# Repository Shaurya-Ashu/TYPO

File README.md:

# TYPO
It is a 80% keyboard containing 79 keys 1 rotary encoder and a custom touchpad button all together is powered by a raspberry pi pico .

# Schematics 
In KiCad 

# PCB 
It's a 2 layer simple pcb designed in KiCad .

it has a one pice silkscreen on the back 

# Case
It's a very simple case designed in fusion 360 .
It is designed around integrated plate mount with bottom plate .

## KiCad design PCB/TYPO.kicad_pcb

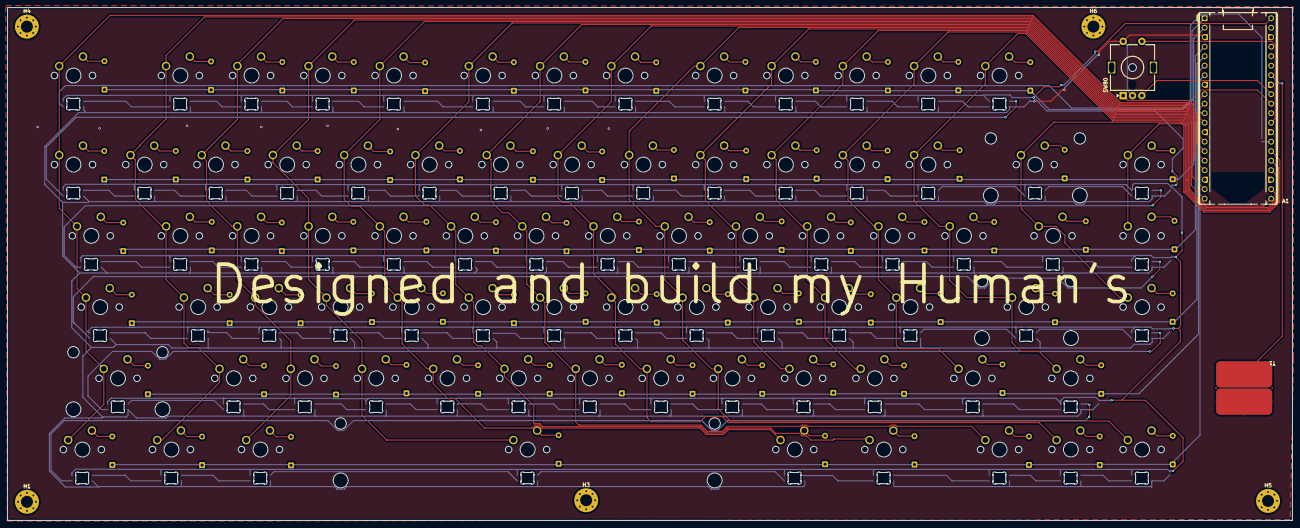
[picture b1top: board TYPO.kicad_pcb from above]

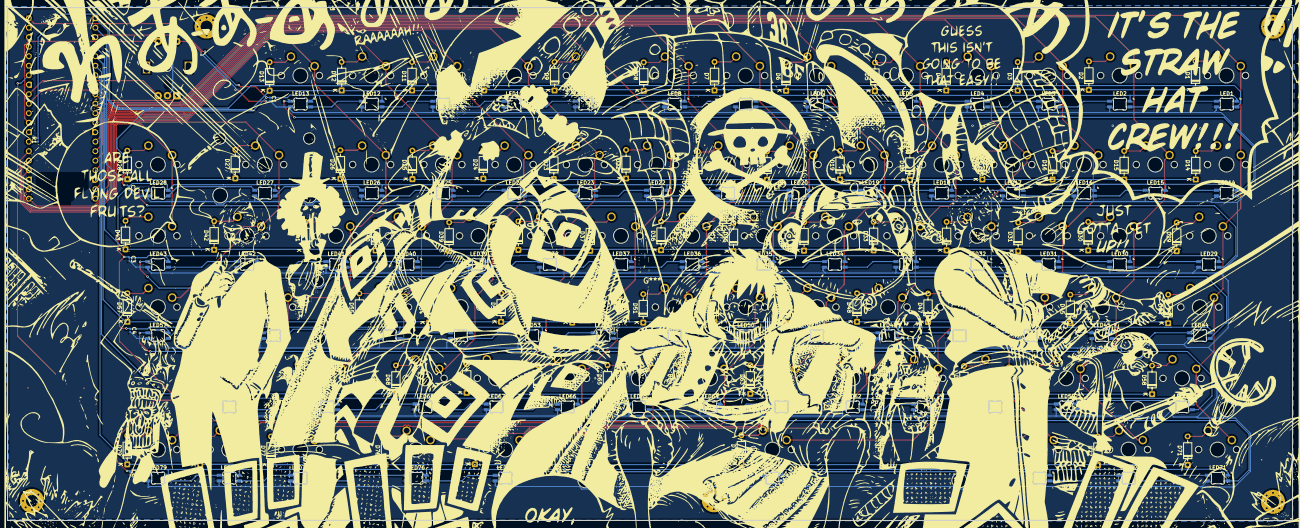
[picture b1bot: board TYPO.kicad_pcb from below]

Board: 2 copper layers, 343.6 x 137.1 mm, 256 parts (165 on the bottom side), 186 nets.

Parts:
A1: RaspberryPi_Pico; RaspberryPi_Pico_Common_THT
C1, C2, C3, C4, C5, C6: C; C_0201_0603Metric_Pad0.64x0.40mm_HandSolder
D1, D2, D3, D4, D5, D6, D7, D8, D9, D10, D11, D12, D13, D14, D15, D16, D17, D18, D19, D20, D21, D22, D23, D24, D25, D26, D27, D28, D29, D30, D31, D32, D33, D34, D35, D36, D37, D38, D39, D40, D41, D42, D43, D44, D45, D46, D47, D48, D49, D50, D51, D52, D53, D54, D55, D56, D57, D58, D59, D60, D61, D62, D63, D64, D65, D66, D67, D68, D69, D70, D71, D72, D73, D74, D75, D76, D77, D78, D79: 1N4148; D_DO-35_SOD27_P7.62mm_Horizontal
H1, H3, H4, H5, H6: MountingHole; MountingHole_3.2mm_M3_Pad_Via
LED1, LED2, LED3, LED4, LED5, LED6, LED7, LED8, LED9, LED10, LED11, LED12, LED13, LED14, LED15, LED16, LED17, LED18, LED19, LED20, LED21, LED22, LED23, LED24, LED25, LED26, LED27, LED28, LED29, LED30, LED31, LED32, LED33, LED34, LED35, LED36, LED37, LED38, LED39, LED40, LED41, LED42, LED43, LED44, LED45, LED46, LED47, LED48, LED49, LED50, LED51, LED52, LED53, LED54, LED55, LED56, LED57, LED58, LED59, LED60, LED61, LED62, LED63, LED64, LED65, LED66, LED67, LED68, LED69, LED70, LED71, LED72, LED73, LED74, LED75, LED76, LED77, LED78, LED79: SK6812MINI-E; LED_6028R
R1: R; R_0201_0603Metric_Pad0.64x0.40mm_HandSolder
S1: MX_stab; STAB_MX_6.25u
S2, S3: MX_stab; STAB_MX_2.25u
S4: MX_stab; STAB_MX_2u
SW1, SW2, SW3, SW4, SW5, SW6, SW7, SW8, SW9, SW10, SW11, SW12, SW13, SW14, SW15, SW16, SW17, SW18, SW19, SW20, SW21, SW22, SW23, SW24, SW25, SW26, SW27, SW28, SW29, SW30, SW31, SW32, SW33, SW34, SW35, SW36, SW37, SW38, SW39, SW40, SW41, SW42, SW43, SW44, SW45, SW46, SW47, SW48, SW49, SW50, SW51, SW52, SW53, SW54, SW55, SW56, SW57, SW58, SW59, SW60, SW61, SW62, SW63, SW64, SW65, SW66, SW67, SW68, SW69, SW70, SW71, SW72, SW73, SW74, SW75, SW76, SW77, SW78, SW79: SW_Push; SW_MX_1u
SW80: RotaryEncoder_Switch_MP; RotaryEncoder_Alps_EC11E-Switch_Vertical_H20mm_MountingHoles
T1: touch

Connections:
/A: A1.31 (GPIO26_ADC0), SW80.A
/B: A1.32 (GPIO27_ADC1), SW80.B
/C1: A1.9 (GPIO6), SW1.1, SW14.1, SW29.1, SW44.1, SW58.1, SW71.1
/C2: A1.10 (GPIO7), SW2.1, SW15.1, SW30.1, SW45.1, SW59.1, SW72.1
/C3: A1.11 (GPIO8), SW3.1, SW16.1, SW31.1, SW46.1, SW60.1, SW73.1
/C4: A1.12 (GPIO9), SW4.1, SW17.1, SW32.1, SW47.1, SW61.1, SW74.1
/C5: A1.14 (GPIO10), SW5.1, SW18.1, SW33.1, SW48.1, SW62.1, SW75.1
/C6: A1.15 (GPIO11), SW6.1, SW19.1, SW34.1, SW49.1, SW63.1, SW76.1
/C7: A1.16 (GPIO12), SW7.1, SW20.1, SW35.1, SW50.1, SW64.1, SW77.1
/C8: A1.17 (GPIO13), SW8.1, SW21.1, SW36.1, SW51.1, SW65.1, SW78.1
/C9: A1.19 (GPIO14), SW9.1, SW22.1, SW37.1, SW52.1, SW66.1, SW79.1
/C10: A1.20 (GPIO15), SW10.1, SW23.1, SW38.1, SW53.1, SW67.1
/C11: A1.21 (GPIO16), SW11.1, SW24.1, SW39.1, SW54.1, SW68.1
/C12: A1.22 (GPIO17), SW12.1, SW25.1, SW40.1, SW55.1, SW69.1
/C13: A1.24 (GPIO18), SW13.1, SW26.1, SW41.1, SW56.1, SW70.1
/C14: A1.25 (GPIO19), SW27.1, SW42.1, SW57.1
/C15: A1.26 (GPIO20), SW28.1, SW43.1
/R1: A1.1 (GPIO0), D1.1 (K), D2.1 (K), D3.1 (K), D4.1 (K), D5.1 (K), D6.1 (K), D7.1 (K), D8.1 (K), D9.1 (K), D10.1 (K), D11.1 (K), D12.1 (K), D13.1 (K)
/R2: A1.2 (GPIO1), D14.1 (K), D15.1 (K), D16.1 (K), D17.1 (K), D18.1 (K), D19.1 (K), D20.1 (K), D21.1 (K), D22.1 (K), D23.1 (K), D24.1 (K), D25.1 (K), D26.1 (K), D27.1 (K), D28.1 (K)
/R3: A1.4 (GPIO2), D29.1 (K), D30.1 (K), D31.1 (K), D32.1 (K), D33.1 (K), D34.1 (K), D35.1 (K), D36.1 (K), D37.1 (K), D38.1 (K), D39.1 (K), D40.1 (K), D41.1 (K), D42.1 (K), D43.1 (K)
/R4: A1.5 (GPIO3), D44.1 (K), D45.1 (K), D46.1 (K), D47.1 (K), D48.1 (K), D49.1 (K), D50.1 (K), D51.1 (K), D52.1 (K), D53.1 (K), D54.1 (K), D55.1 (K), D56.1 (K), D57.1 (K)
/R5: A1.6 (GPIO4), D58.1 (K), D59.1 (K), D60.1 (K), D61.1 (K), D62.1 (K), D63.1 (K), D64.1 (K), D65.1 (K), D66.1 (K), D67.1 (K), D68.1 (K), D69.1 (K), D70.1 (K)
/R6: A1.7 (GPIO5), D71.1 (K), D72.1 (K), D73.1 (K), D74.1 (K), D75.1 (K), D76.1 (K), D77.1 (K), D78.1 (K), D79.1 (K)
/SW1: A1.29 (GPIO22), SW80.S1
/touch: A1.34 (GPIO28_ADC2), T1.1 (out)
GND: A1.3 (GND), A1.8 (GND), A1.13 (GND), A1.18 (GND), A1.23 (GND), A1.28 (GND), A1.38 (GND), C1.2, C2.2, C3.2, C4.2, C5.2, C6.2, LED1.1 (VDD), LED2.1 (VDD), LED3.1 (VDD), LED4.1 (VDD), LED5.1 (VDD), LED6.1 (VDD), LED7.1 (VDD), LED8.1 (VDD), LED9.1 (VDD), LED10.1 (VDD), LED11.1 (VDD), LED12.1 (VDD), LED13.1 (VDD), LED14.1 (VDD), LED15.1 (VDD), LED16.1 (VDD), LED17.1 (VDD), LED18.1 (VDD), LED19.1 (VDD), LED20.1 (VDD), LED21.1 (VDD), LED22.1 (VDD), LED23.1 (VDD), LED24.1 (VDD), LED25.1 (VDD), LED26.1 (VDD), LED27.1 (VDD), LED28.1 (VDD), LED29.1 (VDD), LED30.1 (VDD), LED31.1 (VDD), LED32.1 (VDD), LED33.1 (VDD), LED34.1 (VDD), LED35.1 (VDD), LED36.1 (VDD), LED37.1 (VDD), LED38.1 (VDD), LED39.1 (VDD), LED40.1 (VDD), LED41.1 (VDD), LED42.1 (VDD), LED43.1 (VDD), LED44.1 (VDD), LED45.1 (VDD), LED46.1 (VDD), LED47.1 (VDD), LED48.1 (VDD), LED49.1 (VDD), LED50.1 (VDD), LED51.1 (VDD), LED52.1 (VDD), LED53.1 (VDD), LED54.1 (VDD), LED55.1 (VDD), LED56.1 (VDD), LED57.1 (VDD), LED58.1 (VDD), LED59.1 (VDD), LED60.1 (VDD), LED61.1 (VDD), LED62.1 (VDD), LED63.1 (VDD), LED64.1 (VDD), LED65.1 (VDD), LED66.1 (VDD), LED67.1 (VDD), LED68.1 (VDD), LED69.1 (VDD), LED70.1 (VDD), LED71.1 (VDD), LED72.1 (VDD), LED73.1 (VDD), LED74.1 (VDD), LED75.1 (VDD), LED76.1 (VDD), LED77.1 (VDD), LED78.1 (VDD), LED79.1 (VDD), SW80.C, SW80.S2, T1.2 (gnd)
unnamed: A1.27 (GPIO21), R1.1
unnamed: D1.2 (A), SW1.2
unnamed: D2.2 (A), SW2.2
unnamed: D3.2 (A), SW3.2
unnamed: D4.2 (A), SW4.2
unnamed: D5.2 (A), SW5.2
unnamed: D6.2 (A), SW6.2
unnamed: D7.2 (A), SW7.2
unnamed: D8.2 (A), SW8.2
unnamed: D9.2 (A), SW9.2
unnamed: D10.2 (A), SW10.2
unnamed: D11.2 (A), SW11.2
unnamed: D12.2 (A), SW12.2
unnamed: D13.2 (A), SW13.2
unnamed: D14.2 (A), SW14.2
unnamed: D15.2 (A), SW15.2
unnamed: D16.2 (A), SW16.2
unnamed: D17.2 (A), SW17.2
unnamed: D18.2 (A), SW18.2
unnamed: D19.2 (A), SW19.2
unnamed: D20.2 (A), SW20.2
unnamed: D21.2 (A), SW21.2
unnamed: D22.2 (A), SW22.2
unnamed: D23.2 (A), SW23.2
unnamed: D24.2 (A), SW24.2
unnamed: D25.2 (A), SW25.2
unnamed: D26.2 (A), SW26.2
unnamed: D27.2 (A), SW27.2
unnamed: D28.2 (A), SW28.2
unnamed: D29.2 (A), SW29.2
unnamed: D30.2 (A), SW30.2
unnamed: D31.2 (A), SW31.2
unnamed: D32.2 (A), SW32.2
unnamed: D33.2 (A), SW33.2
unnamed: D34.2 (A), SW34.2
unnamed: D35.2 (A), SW35.2
unnamed: D36.2 (A), SW36.2
unnamed: D37.2 (A), SW37.2
unnamed: D38.2 (A), SW38.2
unnamed: D39.2 (A), SW39.2
unnamed: D40.2 (A), SW40.2
unnamed: D41.2 (A), SW41.2
unnamed: D42.2 (A), SW42.2
unnamed: D43.2 (A), SW43.2
unnamed: D44.2 (A), SW44.2
unnamed: D45.2 (A), SW45.2
unnamed: D46.2 (A), SW46.2
unnamed: D47.2 (A), SW47.2
unnamed: D48.2 (A), SW48.2
unnamed: D49.2 (A), SW49.2
unnamed: D50.2 (A), SW50.2
unnamed: D51.2 (A), SW51.2
unnamed: D52.2 (A), SW52.2
unnamed: D53.2 (A), SW53.2
unnamed: D54.2 (A), SW54.2
unnamed: D55.2 (A), SW55.2
unnamed: D56.2 (A), SW56.2
unnamed: D57.2 (A), SW57.2
unnamed: D58.2 (A), SW58.2
unnamed: D59.2 (A), SW59.2
unnamed: D60.2 (A), SW60.2
unnamed: D61.2 (A), SW61.2
unnamed: D62.2 (A), SW62.2
unnamed: D63.2 (A), SW63.2
unnamed: D64.2 (A), SW64.2
unnamed: D65.2 (A), SW65.2
unnamed: D66.2 (A), SW66.2
unnamed: D67.2 (A), SW67.2
unnamed: D68.2 (A), SW68.2
unnamed: D69.2 (A), SW69.2
unnamed: D70.2 (A), SW70.2
unnamed: D71.2 (A), SW71.2
unnamed: D72.2 (A), SW72.2
unnamed: D73.2 (A), SW73.2
unnamed: D74.2 (A), SW74.2
unnamed: D75.2 (A), SW75.2
unnamed: D76.2 (A), SW76.2
unnamed: D77.2 (A), SW77.2
unnamed: D78.2 (A), SW78.2
unnamed: D79.2 (A), SW79.2
unnamed: LED1.2 (DOUT), LED2.3 (DIN)
unnamed: LED2.2 (DOUT), LED3.3 (DIN)
unnamed: LED3.2 (DOUT), LED4.3 (DIN)
unnamed: LED4.2 (DOUT), LED5.3 (DIN)
unnamed: LED5.2 (DOUT), LED6.3 (DIN)
unnamed: LED6.2 (DOUT), LED7.3 (DIN)
unnamed: LED7.2 (DOUT), LED8.3 (DIN)
unnamed: LED8.2 (DOUT), LED9.3 (DIN)
unnamed: LED9.2 (DOUT), LED10.3 (DIN)
unnamed: LED10.2 (DOUT), LED11.3 (DIN)
unnamed: LED11.2 (DOUT), LED12.3 (DIN)
unnamed: LED12.2 (DOUT), LED13.3 (DIN)
unnamed: LED13.2 (DOUT), LED14.3 (DIN)
unnamed: LED14.2 (DOUT), LED15.3 (DIN)
unnamed: LED15.2 (DOUT), LED16.3 (DIN)
unnamed: LED16.2 (DOUT), LED17.3 (DIN)
unnamed: LED17.2 (DOUT), LED18.3 (DIN)
unnamed: LED18.2 (DOUT), LED19.3 (DIN)
unnamed: LED19.2 (DOUT), LED20.3 (DIN)
unnamed: LED20.2 (DOUT), LED21.3 (DIN)
unnamed: LED21.2 (DOUT), LED22.3 (DIN)
unnamed: LED22.2 (DOUT), LED23.3 (DIN)
unnamed: LED23.2 (DOUT), LED24.3 (DIN)
unnamed: LED24.2 (DOUT), LED25.3 (DIN)
unnamed: LED25.2 (DOUT), LED26.3 (DIN)
unnamed: LED26.2 (DOUT), LED27.3 (DIN)
unnamed: LED27.2 (DOUT), LED28.3 (DIN)
unnamed: LED28.2 (DOUT), LED29.3 (DIN)
unnamed: LED29.2 (DOUT), LED30.3 (DIN)
unnamed: LED30.2 (DOUT), LED31.3 (DIN)
unnamed: LED31.2 (DOUT), LED32.3 (DIN)
unnamed: LED32.2 (DOUT), LED33.3 (DIN)
unnamed: LED33.2 (DOUT), LED34.3 (DIN)
unnamed: LED34.2 (DOUT), LED35.3 (DIN)
unnamed: LED35.2 (DOUT), LED36.3 (DIN)
unnamed: LED36.2 (DOUT), LED37.3 (DIN)
unnamed: LED37.2 (DOUT), LED38.3 (DIN)
unnamed: LED38.2 (DOUT), LED39.3 (DIN)
unnamed: LED39.2 (DOUT), LED40.3 (DIN)
unnamed: LED40.2 (DOUT), LED41.3 (DIN)
unnamed: LED41.2 (DOUT), LED42.3 (DIN)
unnamed: LED42.2 (DOUT), LED43.3 (DIN)
unnamed: LED43.2 (DOUT), LED44.3 (DIN)
unnamed: LED44.2 (DOUT), LED45.3 (DIN)
unnamed: LED45.2 (DOUT), LED46.3 (DIN)
unnamed: LED46.2 (DOUT), LED47.3 (DIN)
unnamed: LED47.2 (DOUT), LED48.3 (DIN)
unnamed: LED48.2 (DOUT), LED49.3 (DIN)
unnamed: LED49.2 (DOUT), LED50.3 (DIN)
unnamed: LED50.2 (DOUT), LED51.3 (DIN)
unnamed: LED51.2 (DOUT), LED52.3 (DIN)
unnamed: LED52.2 (DOUT), LED53.3 (DIN)
unnamed: LED53.2 (DOUT), LED54.3 (DIN)
unnamed: LED54.2 (DOUT), LED55.3 (DIN)
unnamed: LED55.2 (DOUT), LED56.3 (DIN)
unnamed: LED56.2 (DOUT), LED57.3 (DIN)
unnamed: LED57.2 (DOUT), LED58.3 (DIN)
unnamed: LED58.2 (DOUT), LED59.3 (DIN)
unnamed: LED59.2 (DOUT), LED60.3 (DIN)
unnamed: LED60.2 (DOUT), LED61.3 (DIN)
unnamed: LED61.2 (DOUT), LED62.3 (DIN)
unnamed: LED62.2 (DOUT), LED63.3 (DIN)
unnamed: LED63.2 (DOUT), LED64.3 (DIN)
unnamed: LED64.2 (DOUT), LED65.3 (DIN)
unnamed: LED65.2 (DOUT), LED66.3 (DIN)
unnamed: LED66.2 (DOUT), LED67.3 (DIN)
unnamed: LED67.2 (DOUT), LED68.3 (DIN)
unnamed: LED68.2 (DOUT), LED69.3 (DIN)
unnamed: LED69.2 (DOUT), LED70.3 (DIN)
unnamed: LED70.2 (DOUT), LED71.3 (DIN)
unnamed: LED71.2 (DOUT), LED72.3 (DIN)
unnamed: LED72.2 (DOUT), LED73.3 (DIN)
unnamed: LED73.2 (DOUT), LED74.3 (DIN)
unnamed: LED74.2 (DOUT), LED75.3 (DIN)
unnamed: LED75.2 (DOUT), LED76.3 (DIN)
unnamed: LED76.2 (DOUT), LED77.3 (DIN)
unnamed: LED77.2 (DOUT), LED78.3 (DIN)
unnamed: LED78.2 (DOUT), LED79.3 (DIN)
RGB: LED1.3 (DIN), R1.2
VCC: A1.40 (VBUS), C1.1, C2.1, C3.1, C4.1, C5.1, C6.1, LED1.4 (VSS), LED2.4 (VSS), LED3.4 (VSS), LED4.4 (VSS), LED5.4 (VSS), LED6.4 (VSS), LED7.4 (VSS), LED8.4 (VSS), LED9.4 (VSS), LED10.4 (VSS), LED11.4 (VSS), LED12.4 (VSS), LED13.4 (VSS), LED14.4 (VSS), LED15.4 (VSS), LED16.4 (VSS), LED17.4 (VSS), LED18.4 (VSS), LED19.4 (VSS), LED20.4 (VSS), LED21.4 (VSS), LED22.4 (VSS), LED23.4 (VSS), LED24.4 (VSS), LED25.4 (VSS), LED26.4 (VSS), LED27.4 (VSS), LED28.4 (VSS), LED29.4 (VSS), LED30.4 (VSS), LED31.4 (VSS), LED32.4 (VSS), LED33.4 (VSS), LED34.4 (VSS), LED35.4 (VSS), LED36.4 (VSS), LED37.4 (VSS), LED38.4 (VSS), LED39.4 (VSS), LED40.4 (VSS), LED41.4 (VSS), LED42.4 (VSS), LED43.4 (VSS), LED44.4 (VSS), LED45.4 (VSS), LED46.4 (VSS), LED47.4 (VSS), LED48.4 (VSS), LED49.4 (VSS), LED50.4 (VSS), LED51.4 (VSS), LED52.4 (VSS), LED53.4 (VSS), LED54.4 (VSS), LED55.4 (VSS), LED56.4 (VSS), LED57.4 (VSS), LED58.4 (VSS), LED59.4 (VSS), LED60.4 (VSS), LED61.4 (VSS), LED62.4 (VSS), LED63.4 (VSS), LED64.4 (VSS), LED65.4 (VSS), LED66.4 (VSS), LED67.4 (VSS), LED68.4 (VSS), LED69.4 (VSS), LED70.4 (VSS), LED71.4 (VSS), LED72.4 (VSS), LED73.4 (VSS), LED74.4 (VSS), LED75.4 (VSS), LED76.4 (VSS), LED77.4 (VSS), LED78.4 (VSS), LED79.4 (VSS)
